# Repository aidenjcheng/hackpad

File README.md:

# AIDEN C's HackPad!

## Features

- 4 Switches all with macros (vscode shortcuts mainly)
- 2 LEDs
- Volume knob that controls volume

## CAD

## PCB

| **Schematic**              | **PCB**             |
| -------------------------- | ------------------- |
|  |  |

## Firmware

volume knob and macros for vscode (open terminal, and command palette)

## [Bill of materials](https://raw.githubusercontent.com/aidenjcheng/hackpad/refs/heads/main/HackPad%20BOM.csv)

- 1x 3d Printed Case
- 1x Seeed XIAO RP2040
- 1x EC11 Rotary Encoder
- 4x Cherry MX Switches
- 4x Blank DSA Keycaps
- 2x SK6812 MINI-E LEDs
- 4x M3x16mm screws
- 4x M3x5mx4mm heatset inserts

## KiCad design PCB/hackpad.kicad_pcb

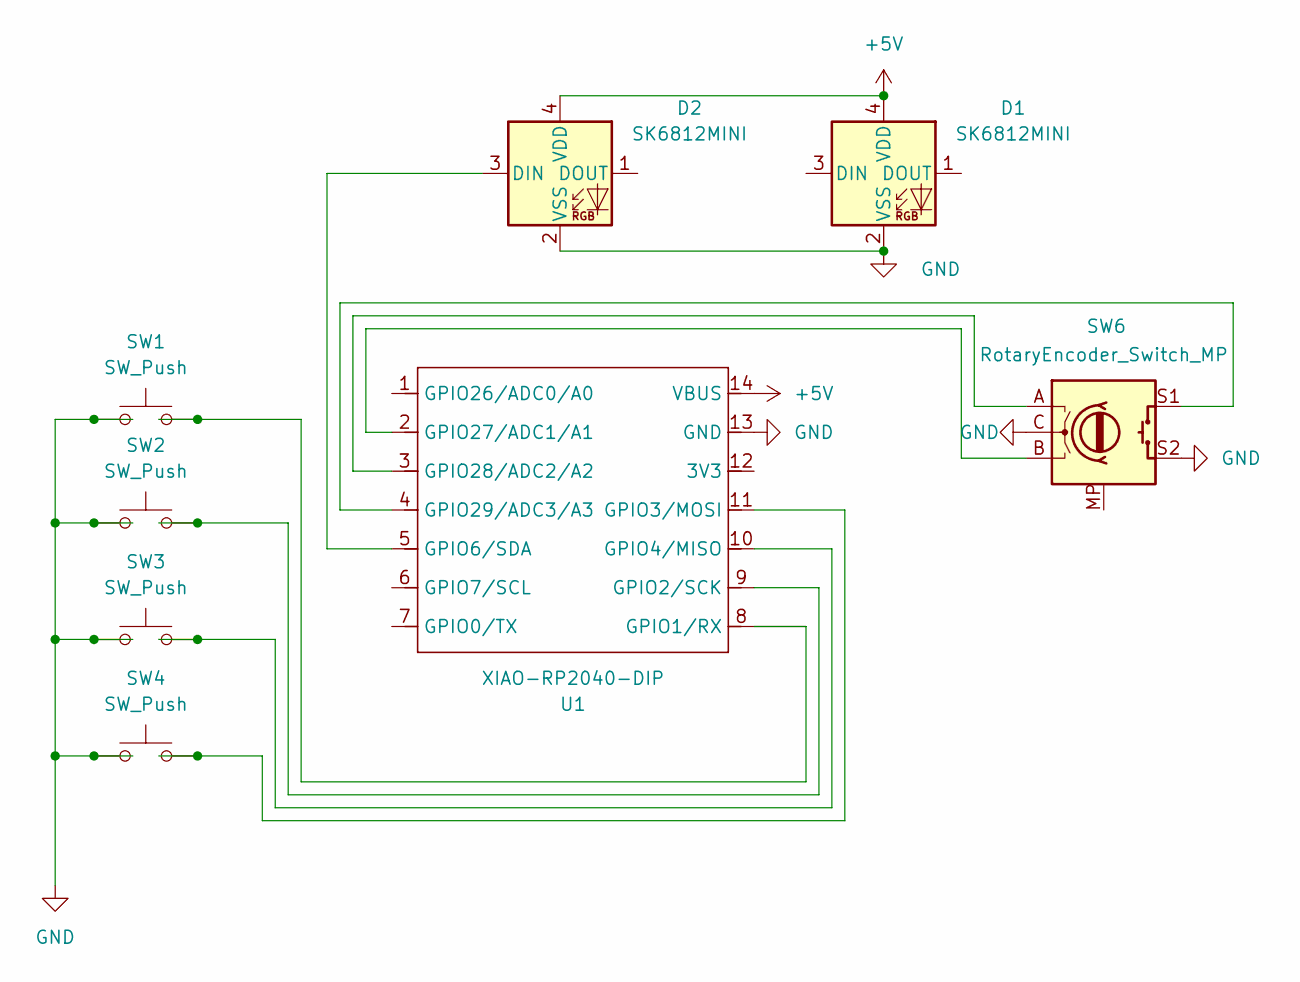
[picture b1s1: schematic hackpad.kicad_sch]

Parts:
D1, D2: SK6812MINI; LED_SK6812MINI_PLCC4_3.5x3.5mm_P1.75mm
SW1, SW2, SW3, SW4: SW_Push; SW_Cherry_MX_1.00u_PCB
SW6: RotaryEncoder_Switch_MP; RotaryEncoder_Alps_EC11E-Switch_Vertical_H20mm
U1: XIAO-RP2040-DIP

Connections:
+5V: D1.4 (VDD), D2.4 (VDD), U1.14 (VBUS)
GND: D1.2 (VSS), D2.2 (VSS), SW1.1, SW2.1, SW3.1, SW4.1, SW6.C, SW6.S2, U1.13 (GND)
unnamed: D2.3 (DIN), U1.5 (GPIO6/SDA)
unnamed: SW1.2, U1.8 (GPIO1/RX)
unnamed: SW2.2, U1.9 (GPIO2/SCK)
unnamed: SW4.2, U1.11 (GPIO3/MOSI)
unnamed: SW3.2, U1.10 (GPIO4/MISO)
unnamed: SW6.B, U1.2 (GPIO27/ADC1/A1)
unnamed: SW6.A, U1.3 (GPIO28/ADC2/A2)
unnamed: SW6.S1, U1.4 (GPIO29/ADC3/A3)

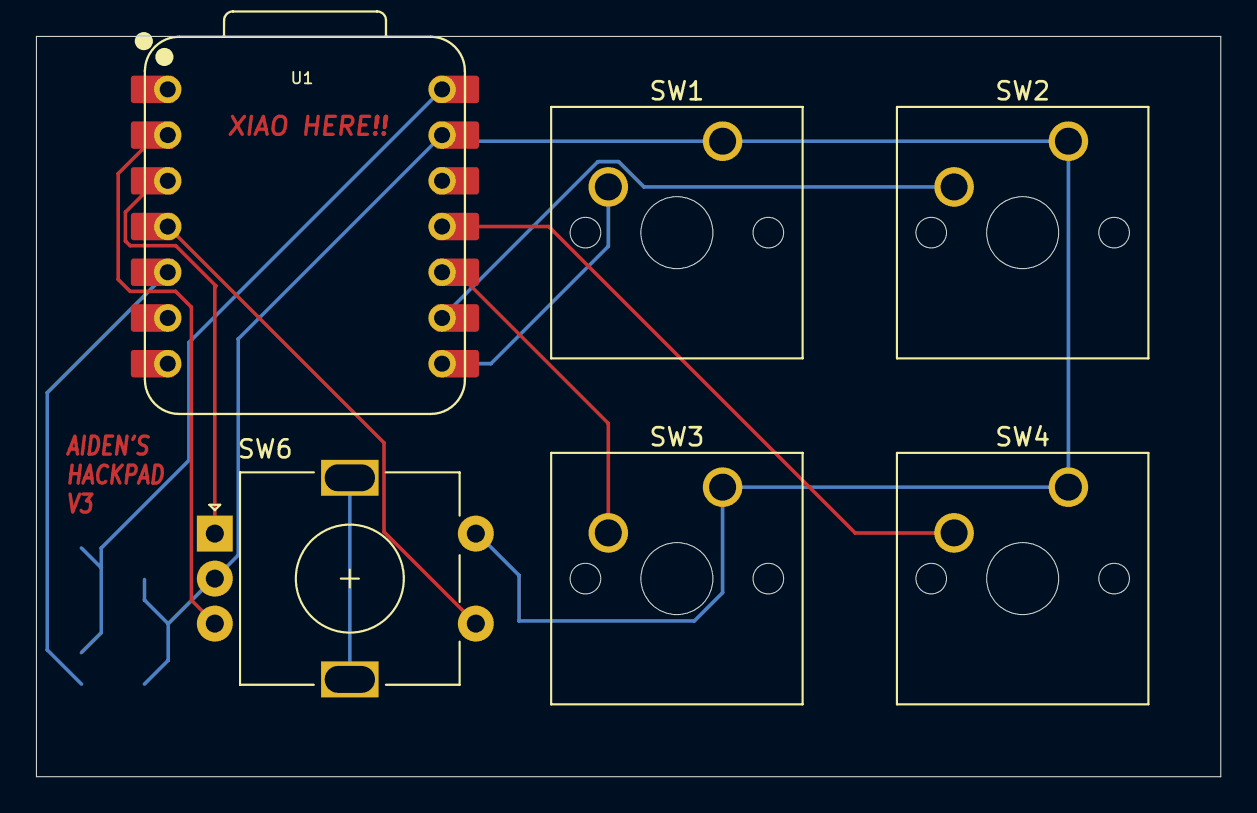
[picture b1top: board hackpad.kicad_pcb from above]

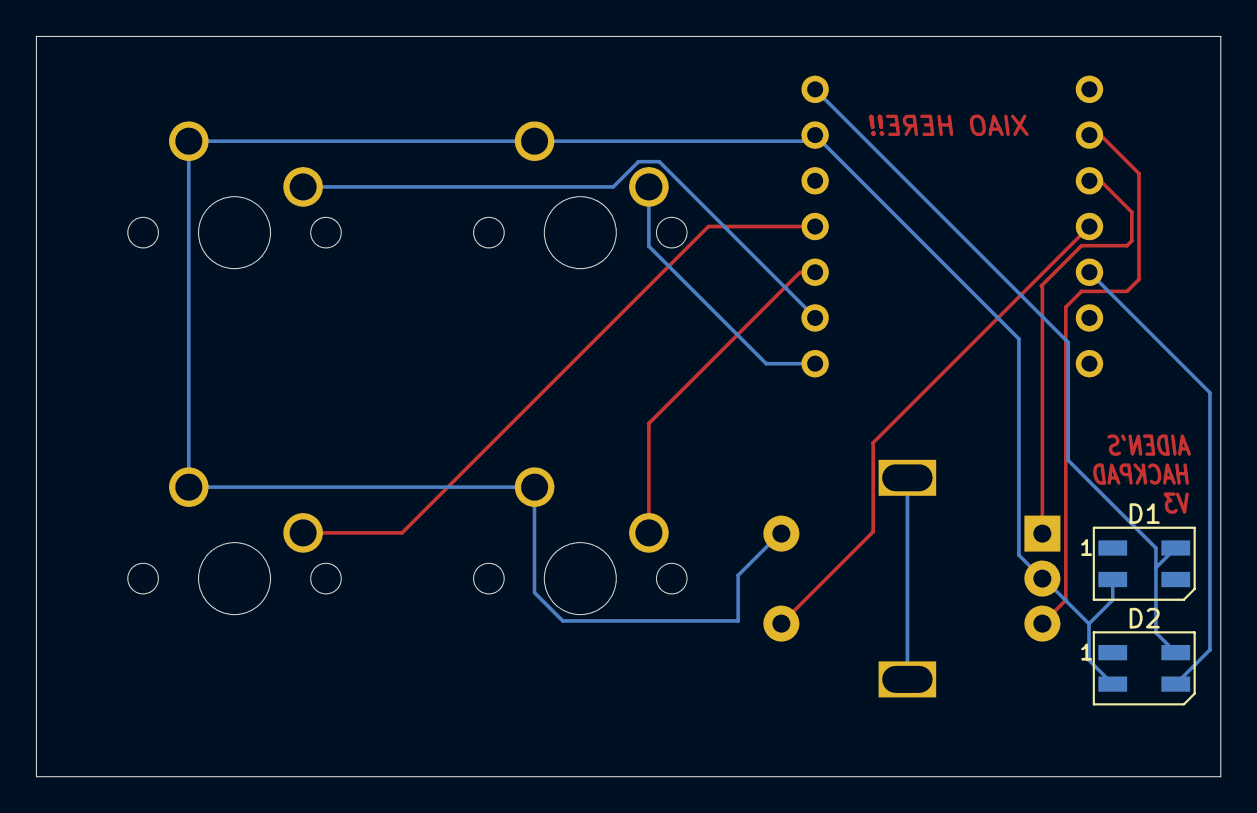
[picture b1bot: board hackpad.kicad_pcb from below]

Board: 2 copper layers, 65.8 x 41.1 mm, 8 parts (2 on the bottom side), 10 nets.

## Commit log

2025-12-03 FINISHED!!!
2025-12-03 update link
